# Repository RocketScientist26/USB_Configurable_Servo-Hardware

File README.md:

# USB Configurable Servo - Hardware

Open source servo motor brain, intended for lab tests and development.

Project page: [https://rocket-scientist.me/servo.html](https://rocket-scientist.me/servo.html)

- Built from vastly available cheap electronic components
- Fully configurable via USB
- Realtime monitoring from Qt app with graphs and controls
- Can be used with ready made cheap mechanical parts, or with your own designs
- Code kept as clean and simple as possible

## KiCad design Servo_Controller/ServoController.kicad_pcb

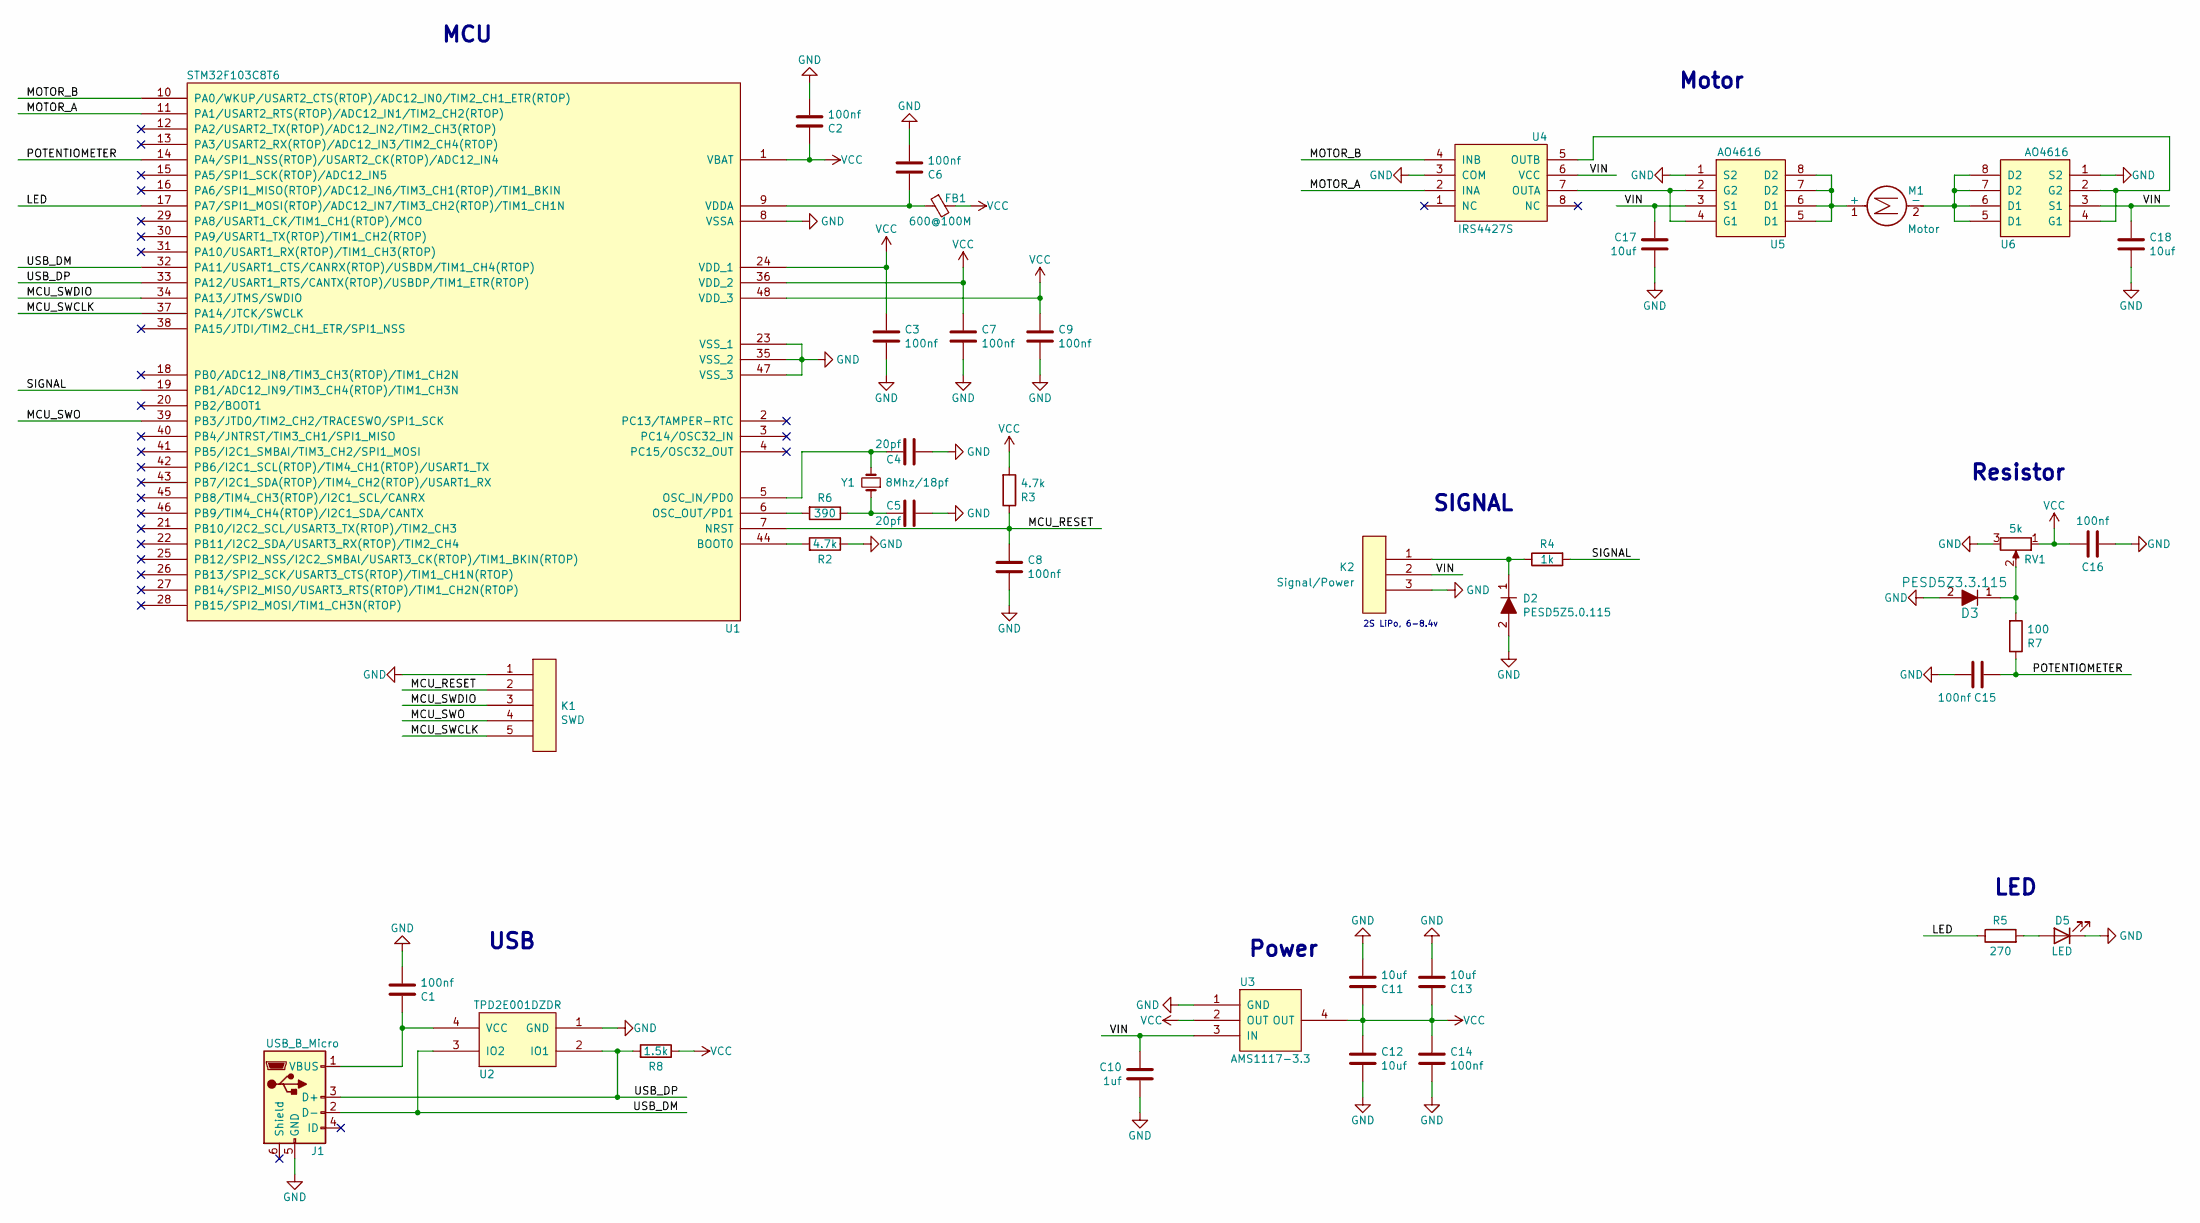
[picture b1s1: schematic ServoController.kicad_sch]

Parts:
C1, C2, C3, C6, C7, C8, C9, C14, C15, C16: 100nf; C_0402
C4, C5: 20pf; C_0402
C10: 1uf; C_0603
C11, C12, C13, C17, C18: 10uf; C_0805
D2: PESD5Z5.0.115; D_SOD-523
D3: PESD5Z3.3.115; D_SOD-523
D5: LED; LED_0402
FB1: 600@100M; L_0805
J1: USB_B_Micro; USB_Micro-B_Molex-105017-0001
K1: SWD
K2: Signal/Power; Signal_Power
M1: Motor
R2, R3: 4.7k; R_0402
R4: 1k; R_0402
R5: 270; R_0402
R6: 390; R_0402
R7: 100; R_0402
R8: 1.5k; R_0402
RV1: 5k; Potentiometer
U1: STM32F103C8T6; LQFP-48
U2: TPD2E001DZDR; DZD
U3: AMS1117-3.3; SOT-223
U4: IRS4427S; SOIC8N
U5, U6: AO4616; SOIC-8
Y1: 8Mhz/18pf; HC-49_US

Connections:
/LED: R5.1, U1.17 (PA7/SPI1_MOSI(RTOP)/ADC12_IN7/TIM3_CH2(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)
/MCU_RESET: C8.1, K1.2, R3.1, U1.7 (NRST)
/MCU_SWCLK: K1.5, U1.37 (PA14/JTCK/SWCLK)
/MCU_SWDIO: K1.3, U1.34 (PA13/JTMS/SWDIO)
/MCU_SWO: K1.4, U1.39 (PB3/JTDO/TIM2_CH2/TRACESWO/SPI1_SCK)
/MOTOR_A: U1.11 (PA1/USART2_RTS(RTOP)/ADC12_IN1/TIM2_CH2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), U4.2 (INA)
/MOTOR_B: U1.10 (PA0/WKUP/USART2_CTS(RTOP)/ADC12_IN0/TIM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), U4.4 (INB)
/POTENTIOMETER: C15.1, R7.1, U1.14 (PA4/SPI1_NSS(RTOP)/USART2_CK(RTOP)/ADC1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)
/SIGNAL: R4.2, U1.19 (PB1/ADC12_IN9/TIM3_CH4(RTOP)/TIM1_CH3N)
/USB_DM: J1.2 (D-), U1.32 (PA11/USART1_CTS/CANRX(RTOP)/USBDM/TIM1_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), U2.3 (IO2)
/USB_DP: J1.3 (D+), R8.2, U1.33 (PA12/USART1_RTS/CANTX(RTOP)/USBDP/TIM1_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), U2.2 (IO1)
/VIN: C10.1, C17.1, C18.1, K2.2, U3.3 (IN), U4.6 (VCC), U5.3 (S1), U6.3 (S1)
GND: C1.2, C2.2, C3.2, C4.2, C5.2, C6.2, C7.2, C8.2, C9.2, C10.2, C11.2, C12.2, C13.2, C14.2, C15.2, C16.2, C17.2, C18.2, D2.2, D3.2, D5.1 (K), J1.5 (GND), K1.1, K2.3, R2.1, RV1.3, U1.8 (VSSA), U1.23 (VSS_1), U1.35 (VSS_2), U1.47 (VSS_3), U2.1 (GND), U3.1 (GND), U4.3 (COM), U5.1 (S2), U6.1 (S2)
unnamed: C1.1, J1.1 (VBUS), U2.4 (VCC)
unnamed: C4.1, U1.5 (OSC_IN/PD0), Y1.2
unnamed: C5.1, R6.1, Y1.1
unnamed: C6.1, FB1.1, U1.9 (VDDA)
unnamed: D2.1, K2.1, R4.1
unnamed: D3.1, R7.2, RV1.2
unnamed: D5.2 (A), R5.2
unnamed: M1.1 (+), U5.5 (D1), U5.6 (D1), U5.7 (D2), U5.8 (D2)
unnamed: M1.2 (-), U6.5 (D1), U6.6 (D1), U6.7 (D2), U6.8 (D2)
unnamed: R2.2, U1.44 (BOOT0)
unnamed: R6.2, U1.6 (OSC_OUT/PD1)
unnamed: U4.5 (OUTB), U6.2 (G2), U6.4 (G1)
unnamed: U4.7 (OUTA), U5.2 (G2), U5.4 (G1)
VCC: C2.1, C3.1, C7.1, C9.1, C11.1, C12.1, C13.1, C14.1, C16.1, FB1.2, R3.2, R8.1, RV1.1, U1.1 (VBAT), U1.24 (VDD_1), U1.36 (VDD_2), U1.48 (VDD_3), U3.2 (OUT), U3.4 (OUT)

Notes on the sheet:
Motor
Resistor
LED
MCU
SIGNAL
USB
Power
2S LiPo, 6-8.4v

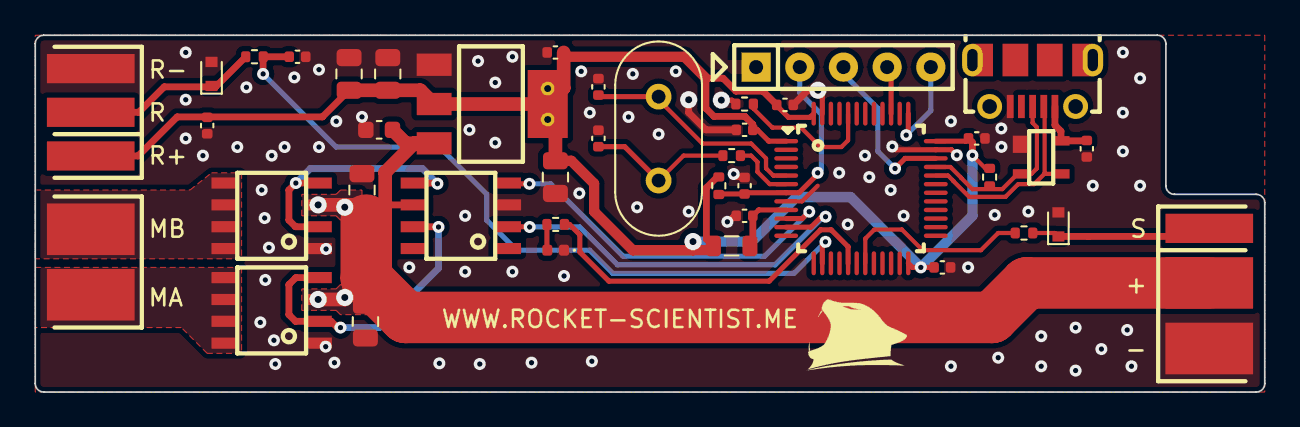
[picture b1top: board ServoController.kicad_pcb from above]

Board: 2 copper layers, 71.5 x 20.8 mm, 42 parts (0 on the bottom side), 27 nets.

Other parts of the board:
VAL: REF; Logo

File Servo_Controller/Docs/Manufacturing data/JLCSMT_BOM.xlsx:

Comment | Designator | Footprint | JLCPCB Part #（optional）
100nf | C1,C2,C3,C6,C7,C8,C9,C14,C15,C16 | SMD_0402 | C110251
20pf | C4,C5 | SMD_0402 | C1554
1uf | C10 | SMD_0603 | C59302
10uf | C11,C12,C13,C17,C18 | SMD_0805 | C95841
PESD5Z5.0.115 | D2 | SOD-523 | C521907
PESD5Z3.3.115 | D3 | SOD-523 | C2892515
Orange LED | D5 | SMD_0402 | C401113
FerriteBead 600 Ohms at 100Mhz | FB1 | SMD_0805 | C98308
USB_Micro-B_Molex-105017-0001 | J1 | SMD_Molex | C132563
4.7k | R2,R3 | SMD_0402 | C304616
1k | R4 | SMD_0402 | C226166
270 Ohms | R5 | SMD_0402 | C25099
390 Ohms | R6 | SMD_0402 | C137997
100 Ohms | R7 | SMD_0402 | C25076
1.5k | R8 | SMD_0402 | C114759
STM32F103CBT6 | U1 | LQFP-48 | C8304
TPD2E001DZDR | U2 | DZD | C89411
AMS1117-3.3 | U3 | SOT-223 | C6186
IRS4427S | U4 | SOIC8N | C171650
AO4616 | U5,U6 | SOIC8 | C115831
Crystal 8Mhz/18pf | Y1 | HC-49_US | C258976

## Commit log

2022-01-05 Update 'README.md'
2022-04-24 Licence added
2022-05-04 Files upload
2022-10-18 Manufacturing data added
2022-10-23 Manual assembly PDF added, value/reference sizes changed in PCB
2022-11-15 Added enclosure, removed unnecessary resistor
2022-11-21 Tester top/bottom photos added
2023-02-06 Changed VCC to SWO signal on SWD header. Manufacturing data and PCB previews updated
2023-02-06 Note.txt text corrected
